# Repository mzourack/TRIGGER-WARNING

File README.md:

# TRIGGER WARNING
passive 2HP Eurorack gate & trigger utility

current version:

PCB V1.1

Panel V1.1

**Features**

Trigger Warning allows you to do a couple of things with gate and trigger signals: 

  -switch between two inputs
  
  -merge two inputs (logical OR)
  
  -mute the output signal
  
  -route the output signal to one of two destination

**Manual**

**Build**

The module is trivial to build - only 12 components are soldered.

Allign the jacks and switches with the pcb and panel as best as possible before soldering. Edges of the plastic body of the jacks can protrude from the 2HP contour of the module if you don't.

**License**

Shield: [![CC BY 4.0][cc-by-shield]][cc-by]

This work is licensed under a
[Creative Commons Attribution 4.0 International License][cc-by].

[![CC BY 4.0][cc-by-image]][cc-by]

[cc-by]: http://creativecommons.org/licenses/by/4.0/
[cc-by-image]: https://i.creativecommons.org/l/by/4.0/88x31.png
[cc-by-shield]: https://img.shields.io/badge/License-CC%20BY%204.0-lightgrey.svg

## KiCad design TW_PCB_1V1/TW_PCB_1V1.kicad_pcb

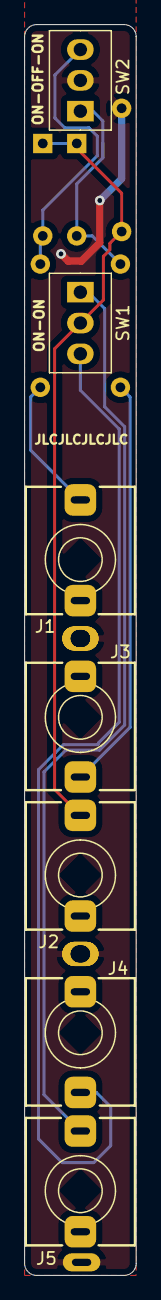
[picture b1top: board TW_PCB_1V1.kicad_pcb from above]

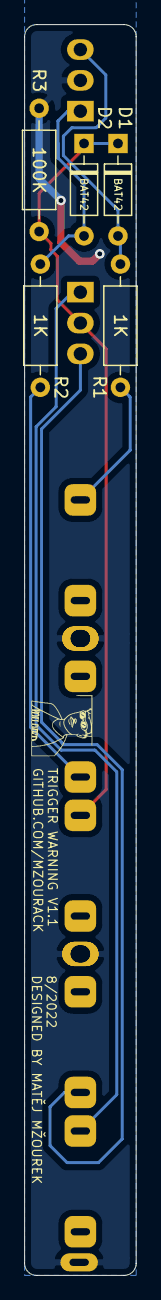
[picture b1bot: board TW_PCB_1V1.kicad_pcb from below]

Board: 2 copper layers, 9.2 x 103.1 mm, 13 parts (6 on the bottom side), 8 nets.

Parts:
D1, D2: BAT42; D_DO-35_SOD27_P7.62mm_Horizontal
J1, J2, J3, J4, J5: Thonkiconn; Jack_3.5mm_QingPu_WQP-PJ398SM_Vertical
R1, R2: 1K; R_Axial_DIN0207_L6.3mm_D2.5mm_P10.16mm_Horizontal
R3: 100K; R_Axial_DIN0207_L6.3mm_D2.5mm_P10.16mm_Horizontal
Ref**: Val**; logo_W8
SW1: SPDT_ON-ON; submini_switch_3_pin
SW2: SPDT_ON-OFF-ON; submini_switch_3_pin

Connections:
GND: J1.S, J2.S, J3.S, J4.S, J5.S, R3.1, SW2.2
unnamed: D1.1 (K), D2.1 (K), J2.T, R3.2, SW1.2 (B)
unnamed: D1.2 (A), R1.2, SW2.3
unnamed: D2.2 (A), R2.2, SW2.1
unnamed: J1.T, R1.1
unnamed: J3.T, R2.1
unnamed: J4.T, SW1.3 (C)
unnamed: J5.T, SW1.1 (A)

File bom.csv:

Designator,Footprint,Quantity,Value,LCSC Part #
J5,Jack_3.5mm_QingPu_WQP-PJ398SM_Vertical,1,Thonkiconn,
J3,Jack_3.5mm_QingPu_WQP-PJ398SM_Vertical,1,Thonkiconn,
J1,Jack_3.5mm_QingPu_WQP-PJ398SM_Vertical,1,Thonkiconn,
J4,Jack_3.5mm_QingPu_WQP-PJ398SM_Vertical,1,Thonkiconn,
J2,Jack_3.5mm_QingPu_WQP-PJ398SM_Vertical,1,Thonkiconn,
D1,D_DO-35_SOD27_P7.62mm_Horizontal,1,BAT42,
D2,D_DO-35_SOD27_P7.62mm_Horizontal,1,BAT42,
SW2,submini_switch_3_pin,1,SPDT_ON-OFF-ON,
SW1,submini_switch_3_pin,1,SPDT_ON-ON,
R3,R_Axial_DIN0207_L6.3mm_D2.5mm_P10.16mm_Horizontal,1,100K,
R2,R_Axial_DIN0207_L6.3mm_D2.5mm_P10.16mm_Horizontal,1,1K,
R1,R_Axial_DIN0207_L6.3mm_D2.5mm_P10.16mm_Horizontal,1,1K,

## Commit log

2023-11-16 readme update
